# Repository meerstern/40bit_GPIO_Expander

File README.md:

# 40Bit GPIO Expander基板

## 概要
 * 本基板は[NXP PCA9506DGG][1]を搭載した40ポートのIO拡張基板です  
 * アドレス変更で同⼀のI2Cバスで最⼤8つ、合計320ポートのIOに拡張することが可能です  
 * 各GPIOはソースで最⼤10mA、シンクで最⼤15mA流すことが可能です  
 * LED等を直接駆動させることが可能です
 * 操作パネル等のGPIOに最適です  
 * 5V/3.3V電源に対応しています  
 * I2CポートにはGrove互換コネクタを搭載しています  
 * デフォルトのI2Cアドレスは0x20(7bit)です  
 * アドレス設定ピンはすべてGNDに接続されています  
 * RESETピンを除く、全GPIO、INT、OEピンにアクセス可能です
 * Arduinoのサンプルプログラムを用意しています   

## 注意点
 * PCA9506DGGはプルアップ抵抗を内蔵していません  
 * スイッチ等の入力で使用する場合は回路に応じて必ずプルダウンかプルアップ抵抗を外付けしてください  
 * 本基板の裏面にプルアップ抵抗の実装パターンがあります  
 * スイッチ等の入力で使用する場合に必要に応じて10k~100kΩ程度の1608サイズ抵抗を実装してください  

  [1]: https://www.nxp.com/products/interfaces/ic-spi-i3c-interface-devices/general-purpose-i-o-gpio/40-bit-ic-bus-i-o-port-with-reset-oe-and-int:PCA9505_06

## 外観
* サイズ 約27mm x約60mm(コネクタ含めず)
* サイズ 約27mm x約63mm(コネクタ含め)

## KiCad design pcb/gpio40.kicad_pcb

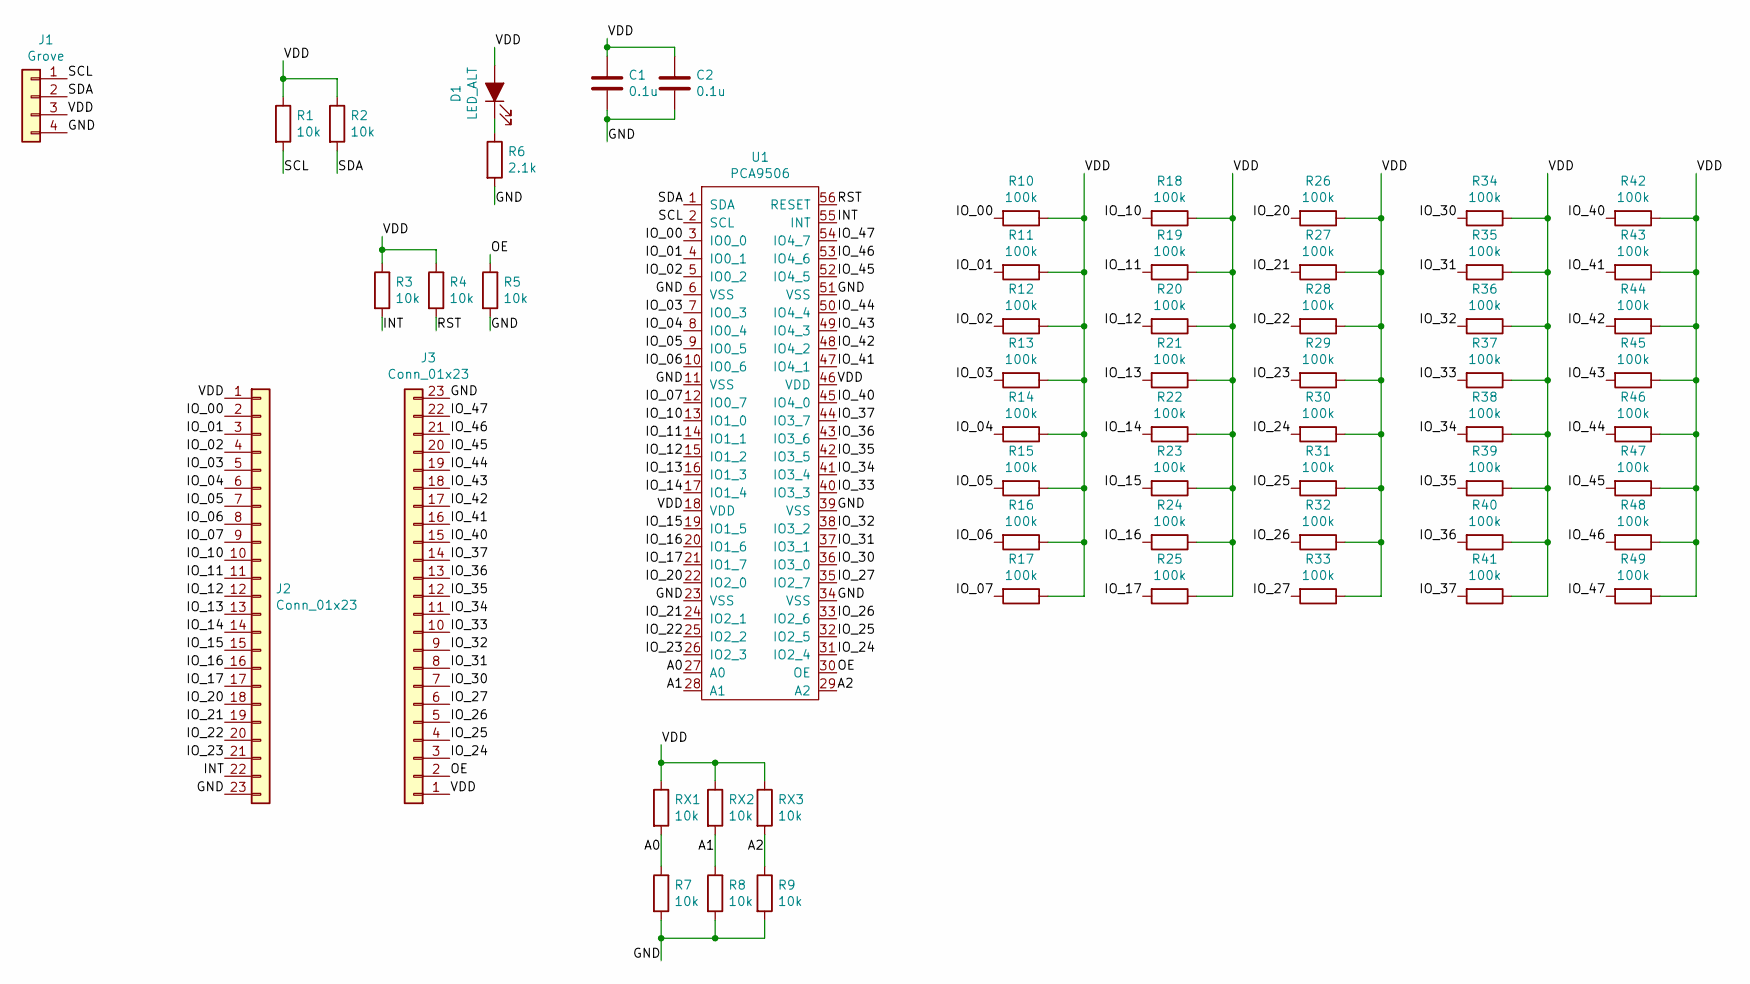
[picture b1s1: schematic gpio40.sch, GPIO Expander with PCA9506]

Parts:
C1, C2: 0.1u; C_0603_1608Metric
D1: LED_ALT; D_0603_1608Metric
J1: Grove; GROVE
J2, J3: Conn_01x23; PinSocket_1x23_P2.54mm_Vertical
R1, R2, R3, R4, R5, R7, R8, R9: 10k; R_0603_1608Metric
R6: 2.1k; R_0603_1608Metric
R10, R11, R12, R13, R14, R15, R16, R17, R18, R19, R20, R21, R22, R23, R24, R25, R26, R27, R28, R29, R30, R31, R32, R33, R34, R35, R36, R37, R38, R39, R40, R41, R42, R43, R44, R45, R46, R47, R48, R49: 100k; R_0603_1608Metric
RX1, RX2, RX3: 10k; R_0603_1608Metric
U1: PCA9506; TSSOP-56_6.1x14mm_P0.5mm

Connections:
/A0: R7.1, RX1.2, U1.27 (A0)
/A1: R8.1, RX2.2, U1.28 (A1)
/A2: R9.1, RX3.2, U1.29 (A2)
/GND: C1.2, C2.2, J1.4, J2.23, J3.23, R5.2, R6.2, R7.2, R8.2, R9.2, U1.6 (VSS), U1.11 (VSS), U1.23 (VSS), U1.34 (VSS), U1.39 (VSS), U1.51 (VSS)
/INT: J2.22, R3.2, U1.55 (INT)
/IO_00: J2.2, R10.2, U1.3 (IO0_0)
/IO_01: J2.3, R11.2, U1.4 (IO0_1)
/IO_02: J2.4, R12.2, U1.5 (IO0_2)
/IO_03: J2.5, R13.2, U1.7 (IO0_3)
/IO_04: J2.6, R14.2, U1.8 (IO0_4)
/IO_05: J2.7, R15.2, U1.9 (IO0_5)
/IO_06: J2.8, R16.2, U1.10 (IO0_6)
/IO_07: J2.9, R17.2, U1.12 (IO0_7)
/IO_10: J2.10, R18.2, U1.13 (IO1_0)
/IO_11: J2.11, R19.2, U1.14 (IO1_1)
/IO_12: J2.12, R20.2, U1.15 (IO1_2)
/IO_13: J2.13, R21.2, U1.16 (IO1_3)
/IO_14: J2.14, R22.2, U1.17 (IO1_4)
/IO_15: J2.15, R23.2, U1.19 (IO1_5)
/IO_16: J2.16, R24.2, U1.20 (IO1_6)
/IO_17: J2.17, R25.2, U1.21 (IO1_7)
/IO_20: J2.18, R26.2, U1.22 (IO2_0)
/IO_21: J2.19, R27.2, U1.24 (IO2_1)
/IO_22: J2.20, R28.2, U1.25 (IO2_2)
/IO_23: J2.21, R29.2, U1.26 (IO2_3)
/IO_24: J3.3, R30.2, U1.31 (IO2_4)
/IO_25: J3.4, R31.2, U1.32 (IO2_5)
/IO_26: J3.5, R32.2, U1.33 (IO2_6)
/IO_27: J3.6, R33.2, U1.35 (IO2_7)
/IO_30: J3.7, R34.2, U1.36 (IO3_0)
/IO_31: J3.8, R35.2, U1.37 (IO3_1)
/IO_32: J3.9, R36.2, U1.38 (IO3_2)
/IO_33: J3.10, R37.2, U1.40 (IO3_3)
/IO_34: J3.11, R38.2, U1.41 (IO3_4)
/IO_35: J3.12, R39.2, U1.42 (IO3_5)
/IO_36: J3.13, R40.2, U1.43 (IO3_6)
/IO_37: J3.14, R41.2, U1.44 (IO3_7)
/IO_40: J3.15, R42.2, U1.45 (IO4_0)
/IO_41: J3.16, R43.2, U1.47 (IO4_1)
/IO_42: J3.17, R44.2, U1.48 (IO4_2)
/IO_43: J3.18, R45.2, U1.49 (IO4_3)
/IO_44: J3.19, R46.2, U1.50 (IO4_4)
/IO_45: J3.20, R47.2, U1.52 (IO4_5)
/IO_46: J3.21, R48.2, U1.53 (IO4_6)
/IO_47: J3.22, R49.2, U1.54 (IO4_7)
/OE: J3.2, R5.1, U1.30 (OE)
/RST: R4.2, U1.56 (RESET)
/SCL: J1.1, R1.2, U1.2 (SCL)
/SDA: J1.2, R2.2, U1.1 (SDA)
/VDD: C1.1, C2.1, D1.2 (A), J1.3, J2.1, J3.1, R1.1, R2.1, R3.1, R4.1, R10.1, R11.1, R12.1, R13.1, R14.1, R15.1, R16.1, R17.1, R18.1, R19.1, R20.1, R21.1, R22.1, R23.1, R24.1, R25.1, R26.1, R27.1, R28.1, R29.1, R30.1, R31.1, R32.1, R33.1, R34.1, R35.1, R36.1, R37.1, R38.1, R39.1, R40.1, R41.1, R42.1, R43.1, R44.1, R45.1, R46.1, R47.1, R48.1, R49.1, RX1.1, RX2.1, RX3.1, U1.18 (VDD), U1.46 (VDD)
unnamed: D1.1 (K), R6.1

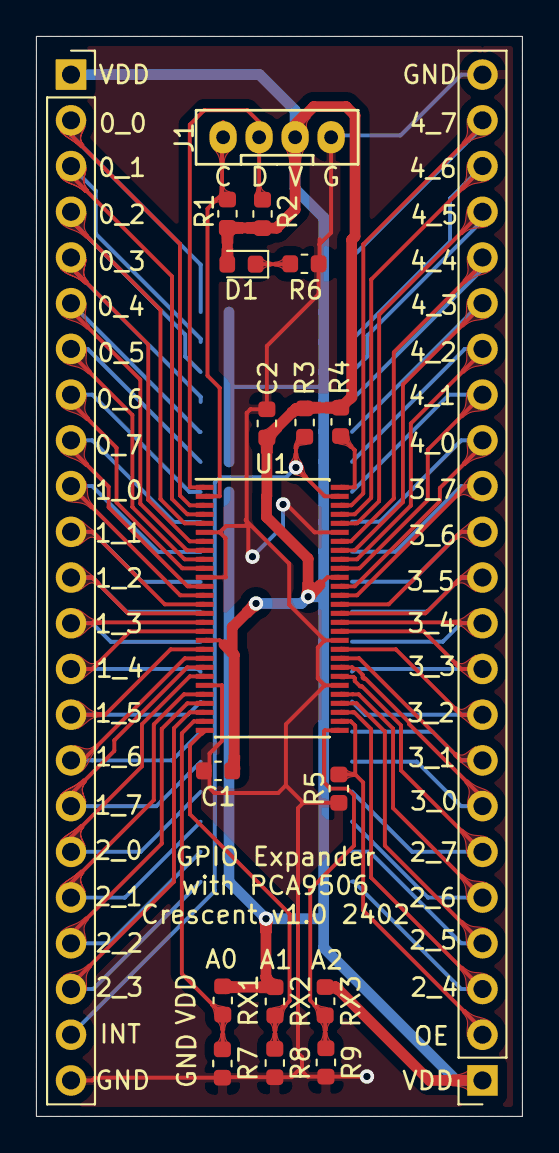
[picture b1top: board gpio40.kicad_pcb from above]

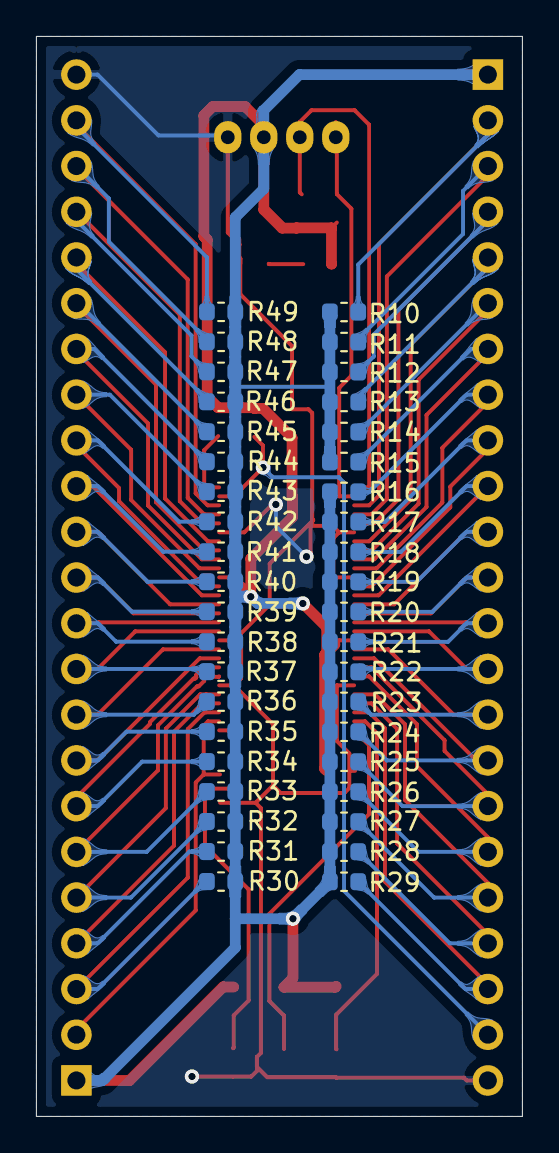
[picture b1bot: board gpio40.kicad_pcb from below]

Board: 2 copper layers, 27.0 x 60.0 mm, 59 parts (40 on the bottom side), 51 nets.

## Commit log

2024-04-13 Add Files
2024-04-13 Add Schematic
